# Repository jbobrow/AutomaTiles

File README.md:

# AutomaTiles

Read [here](GamePlatform.md) to learn about how to think of AutomaTiles as a game platform

AutomaTiles presents a new way to interact with cellular automata. In a physical form, each tile can be manipulated, and progresses based on an external metronome or user input. The same intimate knowledge a movie editor has with a film is shared with computation, as the user can control the speed at which the system evolves and handle individuals as they respond to input.

## Components
1. Virtual AutomaTiles
    1. [Automatiles.com/sim](http://automatiles.com/sim) (written by Jonathan Bobrow, rendered w/ Two.js)
    2. [Automatiles.com/sim/emoji](http://automatiles.com/sim/emoji) (modified version of Nicky Case's Emoji World Simulator)
2. Tangible AutomaTiles
    1. Hardware
        1. Electronics ([Components](https://docs.google.com/spreadsheets/d/1YpmN0rzX8dJSE3OYGx2io3yXud3R6zgf5WAVNdhyiFE))
        2. Printed Circuit Boards ([Rev. 3](http://automatiles.tumblr.com/post/133176987321/rev-3-boards-batch-of-100-automatiles-so-much-to))
        3. [Case Designs + Models](http://automatiles.tumblr.com/post/143452350711/automatiles-w-silicon-jackets-for-members-week)
    2. Firmware
        1. Registers, Pin mapping...
        2. Low Level code not accessible in API
    3. API
        1. [AutomaTile Library](Arduino)
        2. [Documentation](Examples/API.md)
        3. [Example Code](Examples)

##License
Copyright (c) 2015 MIT

Permission is hereby granted, free of charge, to any person obtaining a copy of this software and associated documentation files (the "Software"), to deal in the Software without restriction, including without limitation the rights to use, copy, modify, merge, publish, distribute, sublicense, and/or sell copies of the Software, and to permit persons to whom the Software is furnished to do so, subject to the following conditions:

The above copyright notice and this permission notice shall be included in all copies or substantial portions of the Software.

THE SOFTWARE IS PROVIDED "AS IS", WITHOUT WARRANTY OF ANY KIND, EXPRESS OR IMPLIED, INCLUDING BUT NOT LIMITED TO THE WARRANTIES OF MERCHANTABILITY, FITNESS FOR A PARTICULAR PURPOSE AND NONINFRINGEMENT. IN NO EVENT SHALL THE AUTHORS OR COPYRIGHT HOLDERS BE LIABLE FOR ANY CLAIM, DAMAGES OR OTHER LIABILITY, WHETHER IN AN ACTION OF CONTRACT, TORT OR OTHERWISE, ARISING FROM, OUT OF OR IN CONNECTION WITH THE SOFTWARE OR THE USE OR OTHER DEALINGS IN THE SOFTWARE.

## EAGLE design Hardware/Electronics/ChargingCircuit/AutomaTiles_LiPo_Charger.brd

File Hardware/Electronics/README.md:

##AutomaTiles Electronics##
-	Eagle Parts (Library)
-	Schematics
-	Boards
-	Build of Materials (BOM)
-	Datasheets (maybe just links)

... anything else relevant to electronics

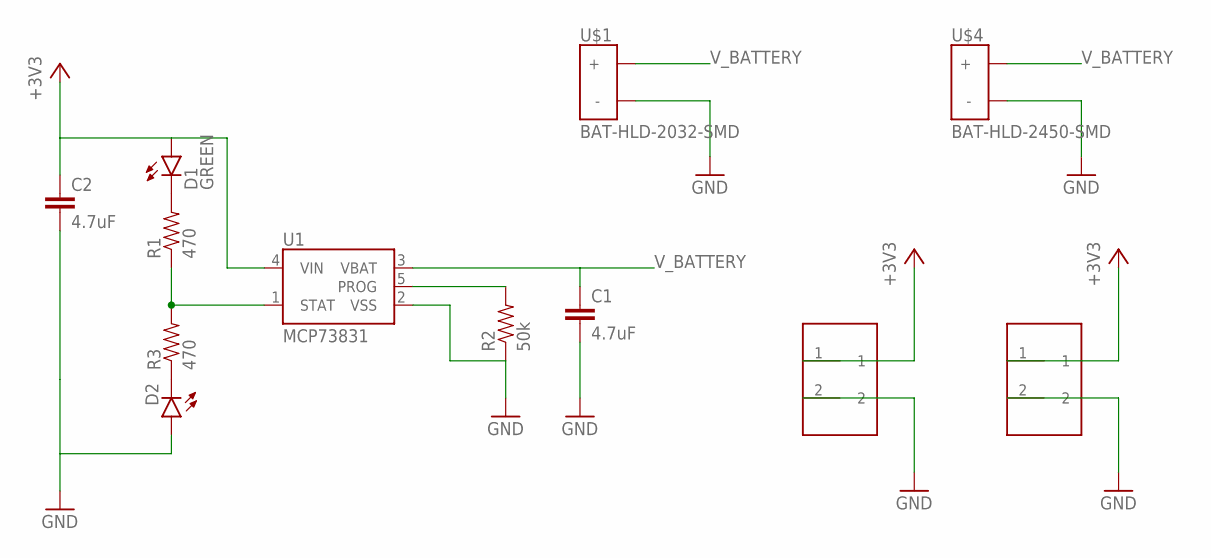
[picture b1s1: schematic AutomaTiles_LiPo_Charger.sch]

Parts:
C1, C2: 4.7uF; 0603-CAP
D1: GREEN; LED-0603
D2: LED-YELLOW0603; LED-0603
R1, R3: 470; 0603-RES
R2: 50k; 0603-RES
U1: MCP73831; SOT23-5
U$1: BAT-HLD-2032-SMD
U$2, U$3: 1X2_FEMALE_HEADER
U$4: BAT-HLD-2450-SMD

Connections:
+3V3: C2.1, D1.A, U1.4 (VIN), U$2.1, U$3.1
GND: C1.2, C2.2, D2.A, R2.1, U1.2 (VSS), U$1.GND (-), U$2.2, U$3.2, U$4.GND (-)
unnamed: R1.1, R3.2, U1.1 (STAT)
unnamed: R2.2, U1.5 (PROG)
unnamed: D1.C, R1.2
unnamed: D2.C, R3.1
V_BATTERY: C1.1, U1.3 (VBAT), U$1.POS1 (+), U$1.POS2 (+), U$4.POS1 (+), U$4.POS2 (+)

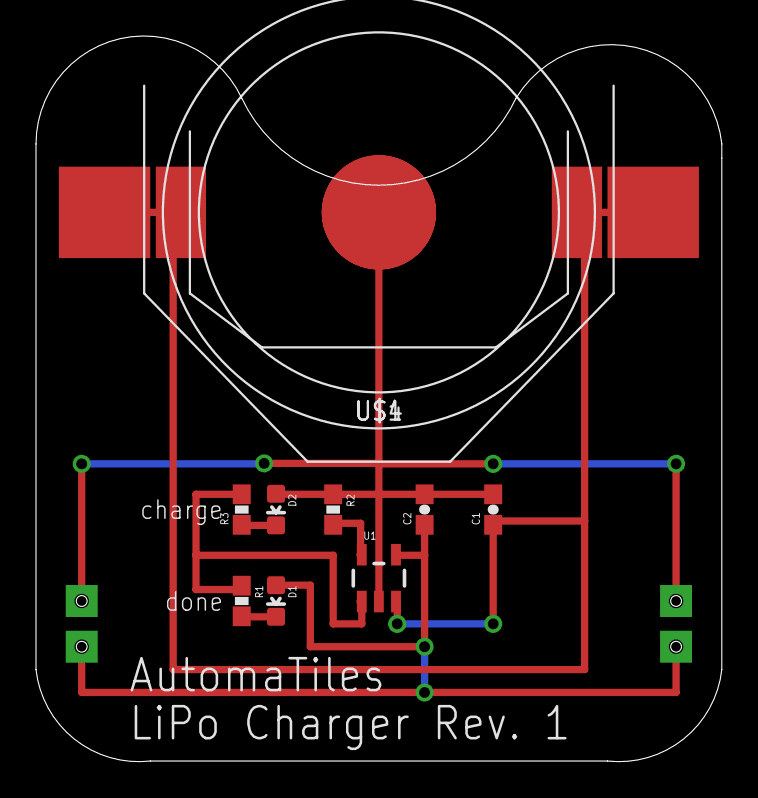
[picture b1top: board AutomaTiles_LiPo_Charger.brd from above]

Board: 2 copper layers, 38.1 x 40.3 mm, 12 parts (0 on the bottom side), 7 nets.

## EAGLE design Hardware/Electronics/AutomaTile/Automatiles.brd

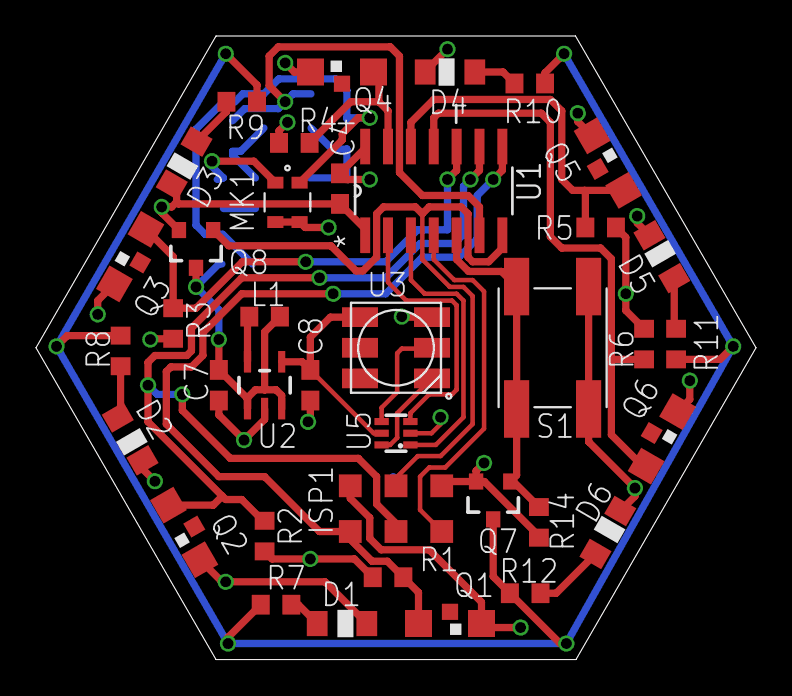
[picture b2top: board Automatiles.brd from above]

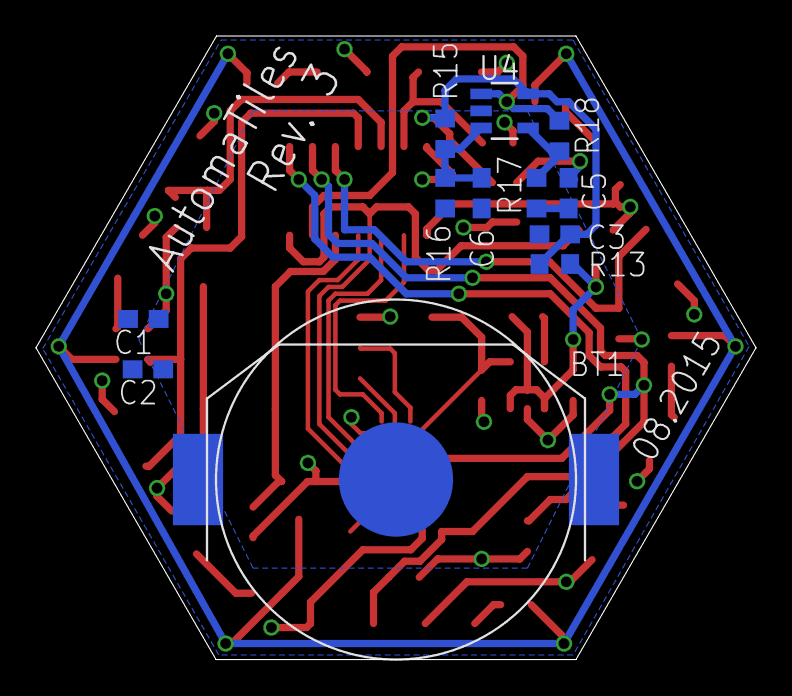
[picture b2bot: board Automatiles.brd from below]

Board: 2 copper layers, 40.0 x 34.6 mm, 50 parts (12 on the bottom side), 31 nets.

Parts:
BT1: BAT-HLD-2032-SMD
C1, C5: 1uF; C0603
C2, C3, C7, C8: 10uF; C0603
C4, C6: 100nF; C0603
D1, D2, D3, D4, D5, D6: LED-SIDELOOKING-IR26-51C; LED-SIDELOOKING
ISP1: AVRISP-POGO
L1: 4.7uH; R0603
MK1: MICROPHONE-MEMS; MEMS-MIC
Q1, Q2, Q3, Q4, Q5, Q6: PHOTOTRANSISTOR-SFH-325LOW-PROFILE; SMD-PHOTOTRANSISTOR-LP
Q7: BSS138; SOT23-3
Q8: BSS84; SOT23-3
R1, R2, R3, R4, R5, R6, R14, R15, R16: 22k; R0603
R7, R8, R9, R10, R11, R12: 2k; R0603
R13: 470; R0603
R17: 1k; R0603
R18: 100k; R0603
S1: TACT-SWITCH-GENERAL; TACT-SWITCH-6MM
U1: ATTINY84-20SSU; SOIC127P600X175-14N
U2: DC-DC-BOOST-XC9140; SOT-23-5
U3: APA102C; WS2812
U4: MCP601OT; SOT23-5
U5: 74HCT2G17; SOT363

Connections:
5V: C8.2, U2.VOUT, U3.NC, U5.5
GND: BT1.GND, C1.1, C2.1, C3.1, C4.2, C6.2, C7.1, C8.1, ISP1.GND, MK1.GNDA, MK1.GNDB, Q7.2, R1.1, R2.1, R3.1, R4.1, R5.1, R6.1, R14.2, R16.2, U1.14, U2.GND, U3.VDD, U4.2, U5.2
LX: L1.2, U2.LX
unnamed: U1.2, U5.3
unnamed: U1.3, U5.1
unnamed: D1.C, R7.2
unnamed: D2.C, R8.2
unnamed: D3.C, R9.2
unnamed: D4.C, R10.2
unnamed: D5.C, R11.2
unnamed: D6.C, R12.2
unnamed: Q7.3, R7.1, R8.1, R9.1, R10.1, R11.1, R12.1
unnamed: Q7.1, R14.1, S1.A, S1.A', U1.5
unnamed: C5.2, MK1.OUTPUT
unnamed: C6.1, R15.2, R16.1, U4.3
unnamed: R17.1, R18.2, U4.4
unnamed: U3.DI, U5.4
unnamed: R18.1, U1.6, U4.1
unnamed: U3.DO, U5.6
unnamed: ISP1.RESET, U1.4
unnamed: ISP1.MOSI, Q8.1, U1.7
PHOTO0: ISP1.MISO, Q1.EMITTER, R1.2, U1.8
PHOTO1: ISP1.SCK, Q2.EMITTER, R2.2, U1.9
PHOTO2: Q3.EMITTER, R3.2, U1.10
PHOTO3: Q4.EMITTER, R4.2, U1.13
PHOTO4: Q5.EMITTER, R5.2, U1.12
PHOTO5: Q6.EMITTER, R6.2, U1.11
TEST: C5.1, R17.2
V+: C3.2, MK1.VCC, R13.2, R15.1, U4.5
VCC: BT1.POS1, BT1.POS2, C1.2, C2.2, C4.1, D1.A, D2.A, D3.A, D4.A, D5.A, D6.A, ISP1.VCC, Q1.COLLECTOR, Q2.COLLECTOR, Q3.COLLECTOR, Q4.COLLECTOR, Q5.COLLECTOR, Q6.COLLECTOR, Q8.2, S1.B, S1.B', U1.1
VCCINT: C7.2, L1.1, Q8.3, R13.1, U2.CE, U2.VBAT

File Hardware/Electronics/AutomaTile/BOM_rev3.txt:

QUANTITY	PART NUMBER	Value	Device	Package	CUSTOMER REFERENCE	Description1	1276-5110-1-ND	100k	R-US_R0603	R0603	R18	"RESISTOR, American symbol"2	490-1532-1-ND	100nF	C-EUC0603	C0603	"C4, C6"	"CAPACITOR, European symbol"4	490-6405-1-ND	10uF	C-EUC0603	C0603	"C2, C3, C7, C8"	"CAPACITOR, European symbol"1	1276-5062-1-ND	1k	R-US_R0603	R0603	R17	"RESISTOR, American symbol"2	490-1549-1-ND	1uF	C-EUC0603	C0603	"C1, C5"	"CAPACITOR, European symbol"9	1276-5094-1-ND	22k	R-US_R0603	R0603	"R1, R2, R3, R4, R5, R6, R14, R15, R16"	"RESISTOR, American symbol"6	1276-5069-1-ND	2k	R-US_R0603	R0603	"R7, R8, R9, R10, R11, R12"	"RESISTOR, American symbol"1	490-4024-1-ND	4.7uH	L-US	R0603	L1	"INDUCTOR, American symbol"1	1276-5054-1-ND	470	R-US_R0603	R0603	R13	"RESISTOR, American symbol"1	568-9252-1-ND	74HCT2G17	74HCT2G17	SOT363	U5	IC BUFF DL SCHM TRG N-INV 6TSSOP1	ATTINY84A-SSURCT-ND	ATTINY84-20SSU	ATTINY84-20SSU	SOIC127P600X175-14N	U1	8-bit Microcontroller with Bytes In-System Programmable Flash1	BK-912-ND	BAT-HLD-2032-SMD	BAT-HLD-2032-SMD	BAT-HLD-2032-SMD	BT1	SMD battery holder for 2032 coincell1	BSS138CT-ND	BSS138	MOSFET-NCHANNELSMD	SOT23-3	Q7	Generic NMOS footprint1	BSS84CT-ND	BSS84	BSS84	SOT23-3	Q8	P-CHANNEL MOS FET1	893-1181-1-ND	DC-DC-BOOST-XC9140	DC-DC-BOOST-XC9140	SOT-23-5	U2	5V output boost converter6	1080-1358-1-ND	LED-SIDELOOKING-IR26-51C	LED-SIDELOOKING-IR26-51C	LED-SIDELOOKING	"D1, D2, D3, D4, D5, D6"	Sidelooking IR LED1	MCP6001T-I/OTCT-ND 	MCP601OT	MCP601OT	SOT23-5	U4	Single Op Amp 2.7V to 6.0V Single Supply CMOS1	423-1394-1-ND 	MICROPHONE-MEMS	MICROPHONE-MEMS	MEMS-MIC	MK1	Mems microphone6	754-1365-1-ND 	PHOTOTRANSISTOR-SFH-325LOW-PROFILE	PHOTOTRANSISTOR-SFH-325LOW-PROFILE	SMD-PHOTOTRANSISTOR-LP	"Q1, Q2, Q3, Q4, Q5, Q6"	Sidelooking NPN phototransistor1	P12970SCT-ND	TACT-SWITCH-GENERAL	TACT-SWITCH-GENERAL	TACT-SWITCH-6MM	S1	General Off-Mom 6mm tactile switch

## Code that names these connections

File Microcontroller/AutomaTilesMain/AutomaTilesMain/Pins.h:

/*
 * Pins.h
 *
 * Created: 7/15/2015 10:59:51
 *  Author: Joshua
 */ 
#include <avr/io.h>

#ifndef PINS_H_
#define PINS_H_
//Phototransistors are mapped out of order for routing purposes
#define PHOTO0 (1<<PA5)
#define PHOTO1 (1<<PA4)
#define PHOTO2 (1<<PA3)
#define PHOTO3 (1<<PA0)
#define PHOTO4 (1<<PA1)
#define PHOTO5 (1<<PA2)
//IR LED output pin
#define IR (1<<PB2)
//LED clock and data pins
#define LEDCLK (1<<PB0)
#define LEDDAT (1<<PB1)
//Microphone pin
#define MIC (1<<PA7)
//Pushbutton pin
#define BUTTON (1<<PB2)
#endif /* PINS_H_ */

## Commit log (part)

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2015-06-16 adding a simulation of 3 regular tesselated shaped and transitions. Need to add neighbor algorithms and GOL logic
2015-06-21 add functionality to control panel, color, and so on
2015-06-21 adding frequency to contol panel and cleaning up buttons. Also added on and off color to each cell
2015-06-21 added neighbor finding function for square and hex, still need to add triangle. Storing neighbor indices
2015-06-21 printing out neighbors for all three shapes
2015-06-22 added comments for simulation and touch events to the cells
2015-06-22 added state to each of the cells. Some minor color adjustments, and initializations
2015-07-14 added simulation logic, running with current neighborhood understanding (needs some updates for edge cases). Pauses simulation when changing shapes
2015-07-14 move folder down and out, excessive nesting
2015-07-14 Added microcontroller project (nothing yet implimented).
2015-07-15 Created Pins file to alias all pin names to their functionality and convert them to masks.
2015-07-15 Added initialization file and function definitions for initialization functions of various systems.
2015-07-15 IO and AD initializations set up.
2015-07-16 add a reset to the control panel
2015-07-16 handle the click on a canvas element for faster rendering, not yet handling the click in each cell
2015-07-21 Altered Clock down to 1MHz for power saving and altered initializations accordingly. Began bringing initializations into main.
2015-07-21 Added code for driving APA102C LED and adjusted some relevant supporting code.
2015-07-21 adding readme to the simulation
2015-07-21 erge
2015-07-22 Currently mic testing.
2015-07-23 Color test
2015-07-27 Removed binary. Updated gitignore. Added microcontroller ReadMe.
2015-07-28 gitignore updates
2015-08-04 System testing
2015-08-05 Minor testing changes, sensitivity adjustment.
2015-08-05 Set up for communicating with surrounding tiles. Misc optimizations.
2015-08-11 Added more testing functions.
2015-08-14 State transmission and detection added. Simple rule set implemented. Small bug fixes.
2015-08-17 Moved IR onto button pin. Tested new System.
2015-08-19 adding a save function to the simulation to export svgs
2015-08-19 update simulation to save svg with a save button. Also change the grid dimensions
2015-08-19 Added detailed commenting to Main
2015-08-19 update shape to default to hexagon
2015-08-20 updated shape update and position update to land in more accurate final locations. helpful for exporting cleaner svgs
2015-08-20 fix vertices bug
2015-09-13 added highlighting of neighbors, fixed hexagonal neighbors, formatted code. Added a save svg feature for export
2015-09-13 highlight as option from control panel
2015-09-14 use shift key to add present, allow to toggle neighbor and regular highlight
2015-09-15 using alt + click inverts self and neighbors, lights out mechanism
2015-09-21 Corrections to help with initialization and click detection accuracy. Build file updated to use debugger.
2015-09-25 Added in synchronization pulses to ensure all boards step together.
2015-09-28 Temporarily disabled microphone. Added button debouncing.
2015-09-29 control panel for ruleset setting, birth and death
2015-09-29 added advanced controls to make all tiles present, all not present, and randomly select tiles to be on
2015-09-29 fixed a comment
2015-10-01 adding stroke width control
2015-10-06 Added cases to ensure that interrupts only behave like mode 0 in mode 0.
2015-10-09 adding web interface for wireless pacemaker
2015-10-09 Added ESP8266 arduino code for communication testing.
2015-10-12 adding readme for arduino sketch
2015-10-15 include other dependencies and change SSID to guest
2015-10-15 hide the ruleset when pressing 'h'
2015-10-15 added controls to the simulation to speed up, slow down from the keyboard
2015-10-15 adding Nancy Liang's php example as a method to update a local json file
2015-10-16 Added power pin. Tweaked configurations slightly for new boards.
2015-10-16 More tweaks for new board
2015-10-19 added toggle for animations, speeds up transition to not animate the move and update of shapes
2015-10-19 Improved pulse robustness
2015-10-23 added a step forward key
2015-10-23 adding a file to start implementing arrangement analysis in JS
2015-10-23 added rulesets for automatiles and an init state
2015-10-23 fixed some syntax in previous ruleset code
2015-10-25 Finished data over IR receiving and retransmitting
2015-10-25 Added and fully tested data parsing, along with a variety of bugfixes for reliable operation. Also added some helper functions for when changing modes.
    In addition, added arduino sketches used for testing pacmaking and data transmission
2015-11-06 Added phototransistor manipulation functions for slight reliability improvement.
2015-11-17 Sleep mode functionality added. Not fully stable. Issues with powerDownTimer.
2015-11-17 prisoners dilemma implemented w/ automatile simulation
2015-11-17 Sleep bugfixes
2015-11-18 disable interrupts when setting a variable equal to timer in microphone handling
2015-11-18 red in state 0, blue/green in state 1
2015-11-24 Code for potentiometer pacemaker w/ arduino
2015-11-24 Made click flashes more subtle.
2015-11-25 adding code for potentiometer pacemaker
2015-12-05 3 species color working with the meta key to switch species... next handle each species ruleset
2015-12-08 removed unused constructor... not sure why it was there in the first place
2016-01-12 Most functions re-implimented in order to allow easy programming by others. button presses and clicks handled through callbacks. Still some bugs to fix regarding sleep mode. Rule retransmission curre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
2016-01-12 Some sleep fixes. Still bugged.
2016-01-15 Added some more interface functions. Cleaned up minor timing issues. did some stress testing.
2016-01-20 Implimented colorful program to test functions. Did some minor bugfixes.
2016-01-22 Fixed and saved rainbow pattern.
2016-01-29 adding code sketches for use with the restructured branch's API
2016-02-03 updated readme to include license and a bit of structure
2016-02-12 Adds user timer callback that operates on ms scales. Closes #6
2016-02-17 updated forest fires comments in header
2016-02-26 Created custom board type for Arduino IDE and modified Arduino core to be compatable with tile. Unstable build. Many things untested. Still modifying structure.
2016-02-29 Update fracture.c
    fixed the formatting to look fine on github or when downloaded
2016-03-18 Fixed timer bug. Callbacks currently non-functional in Arduino. Currently debugging.
2016-03-19 updated forest fire sketch to grow more trees when around trees and have a longer more animated lightning animation
2016-04-02 Fixed ADC problem but disallowing nesred interrupts and removed some long processes from within interrupts to account for change. Some code cleanup is still needed..
2016-04-04 adding wire world to the examples for automatile rulesets
2016-04-08 Added long press detection with associated user settable callback. Fixed slight error in timer interrupt.
2016-04-13 remove pde from sketches
2016-04-13 update the sketches to be arduino friendly
2016-04-15 change fracture change state to require a long press
2016-04-15 Added in data sharing to Arduino core. Not yet tested. Assume Unstable.
2016-04-20 updated simulation to start with hummingbird animation as well as an about page that introduces the various keyboard shortcuts
2016-04-22 added long press overloaded function and check to make sure that long press callback only happens once every long press
2016-04-22 update sketch to latest
2016-04-22 no overloaded functions in C, since the ATTiny requires code from a C compiler
2016-04-22 using uint instead of bool, since c
2016-04-22 click is the same as step, moved button down to where press is handled
2016-04-22 change code sketches folder to examples
2016-04-22 adding fracture back in examples
2016-04-22 adding rock paper scissors
2016-04-22 move wireworld and add comment to fracture
2016-04-22 format comment in wireworld
2016-04-22 update comment to include AutomaTiles board configuration note
2016-04-22 remove c version
2016-04-22 move color gossip, still needs to be finished, but at least it is in the right place with the right formatting
2016-04-22 formatting
2016-04-22 move forest fires to the example folder
2016-04-22 create a wip directory for not yet functioning examples
2016-04-22 adding music visualizer idea to work in progress
2016-04-22 add fft reference for music vis
2016-04-22 removing c sketches
2016-04-22 adding game of life example
2016-04-22 update the api readme to include new functions, long button press and timed callbacks
2016-04-23 adding a readme for the example files
2016-04-23 formatting"
2016-04-25 updated the color gossip sketch to switch states when button pressed and in one state, transition from curent color to cyan in 1 second, and in the other state continue to cycle through all of the co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
2016-04-25 created a color gossip sketch that eases into colors. Still a little buggy from alone state, but close
2016-04-26 updated the color gossip sketch to animate from cyan when cycling... still buggy though
2016-04-26 fixed comment to describe the actual behavior of prototype colors
2016-04-26 update readme with active links
2016-04-26 adding latest examples to the read me and links for references
2016-04-26 move the api out of a folder and into examples as a markdown file to click on
2016-04-26 remove setup from API since it is no longer necessary
2016-04-26 small format fix
2016-04-26 add links to high level readme
2016-05-02 7 color fade to latest color or blink orange if alone. Color doesn't yet take the quickest path
2016-05-02 using the shortest path to animate from one color to the next
2016-05-06 Shared data transmission now fully functional with pulse width 8ms. Data transmission has been tested to be consistent.
2016-05-13 rotating color example working and color gossip is still problematic
2016-05-13 Moved creation of buffers for gossiping into user space to free up large portion of RAM. Issues with color gossip were due to stack overflow corrupting globals. Programs that approach 375+ bytes of g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
2016-05-27 updated color gossip to pulse white when alone, transition via the shortest path, and count if alone properly
2016-05-27 move color gossip to the main folder, since it is complete, and add to the readme
2016-05-27 flash to show heard snap... make fire go out after a single time step
2016-05-27 hardware test to show functionality of all sensors and inputs... starting with microphone
2016-05-27 adding a readme for electronics
2016-05-27 readme for enclosure, soon to add files
2016-05-29 add 2450 battery
2016-05-29 add board design for lipo charger
2016-05-29 adding Rev 3 board and BOM
2016-05-29 update text to lists
2016-06-13 re-adding long press timer
2016-06-13 update fracture to stay brighter and to only change state after 10 confirmations of state change... a debounce for neighbor watching:
2016-06-13 added new battery size and charger parts to eagle library
2016-07-24 adding a lil more detail to the game platform document, testing inserting an image
2016-07-24 adding link for memory management and a lil blurb about the stack
2016-07-24 a note on randomness
2016-10-13 A game of fire and ice in progress
2016-10-20 fixing the states to make them progress towards solved
2016-11-07 updated color gossip to show color changed to during press when alone
2017-01-20 removed discrete time stuff - not working
2017-01-21 udpate git ignore
2017-01-21 update the boards file to show AutomaTiles Legacy
2017-01-21 adding keywords
2017-01-21 adding a progress version of Hot Cold Puzzle..
2017-01-21 changing name of hardware type to AutomaTiles Legacy, to make it clear in Arduino, which version is which
2017-03-30 Update GamePlatform.md
    markdown formatting

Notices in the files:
parts and their libraries:
SparkFun-Capacitors: Licensing: Creative Commons ShareAlike 4.0 International - https://creativecommons.org/licenses/by-sa/4.0
